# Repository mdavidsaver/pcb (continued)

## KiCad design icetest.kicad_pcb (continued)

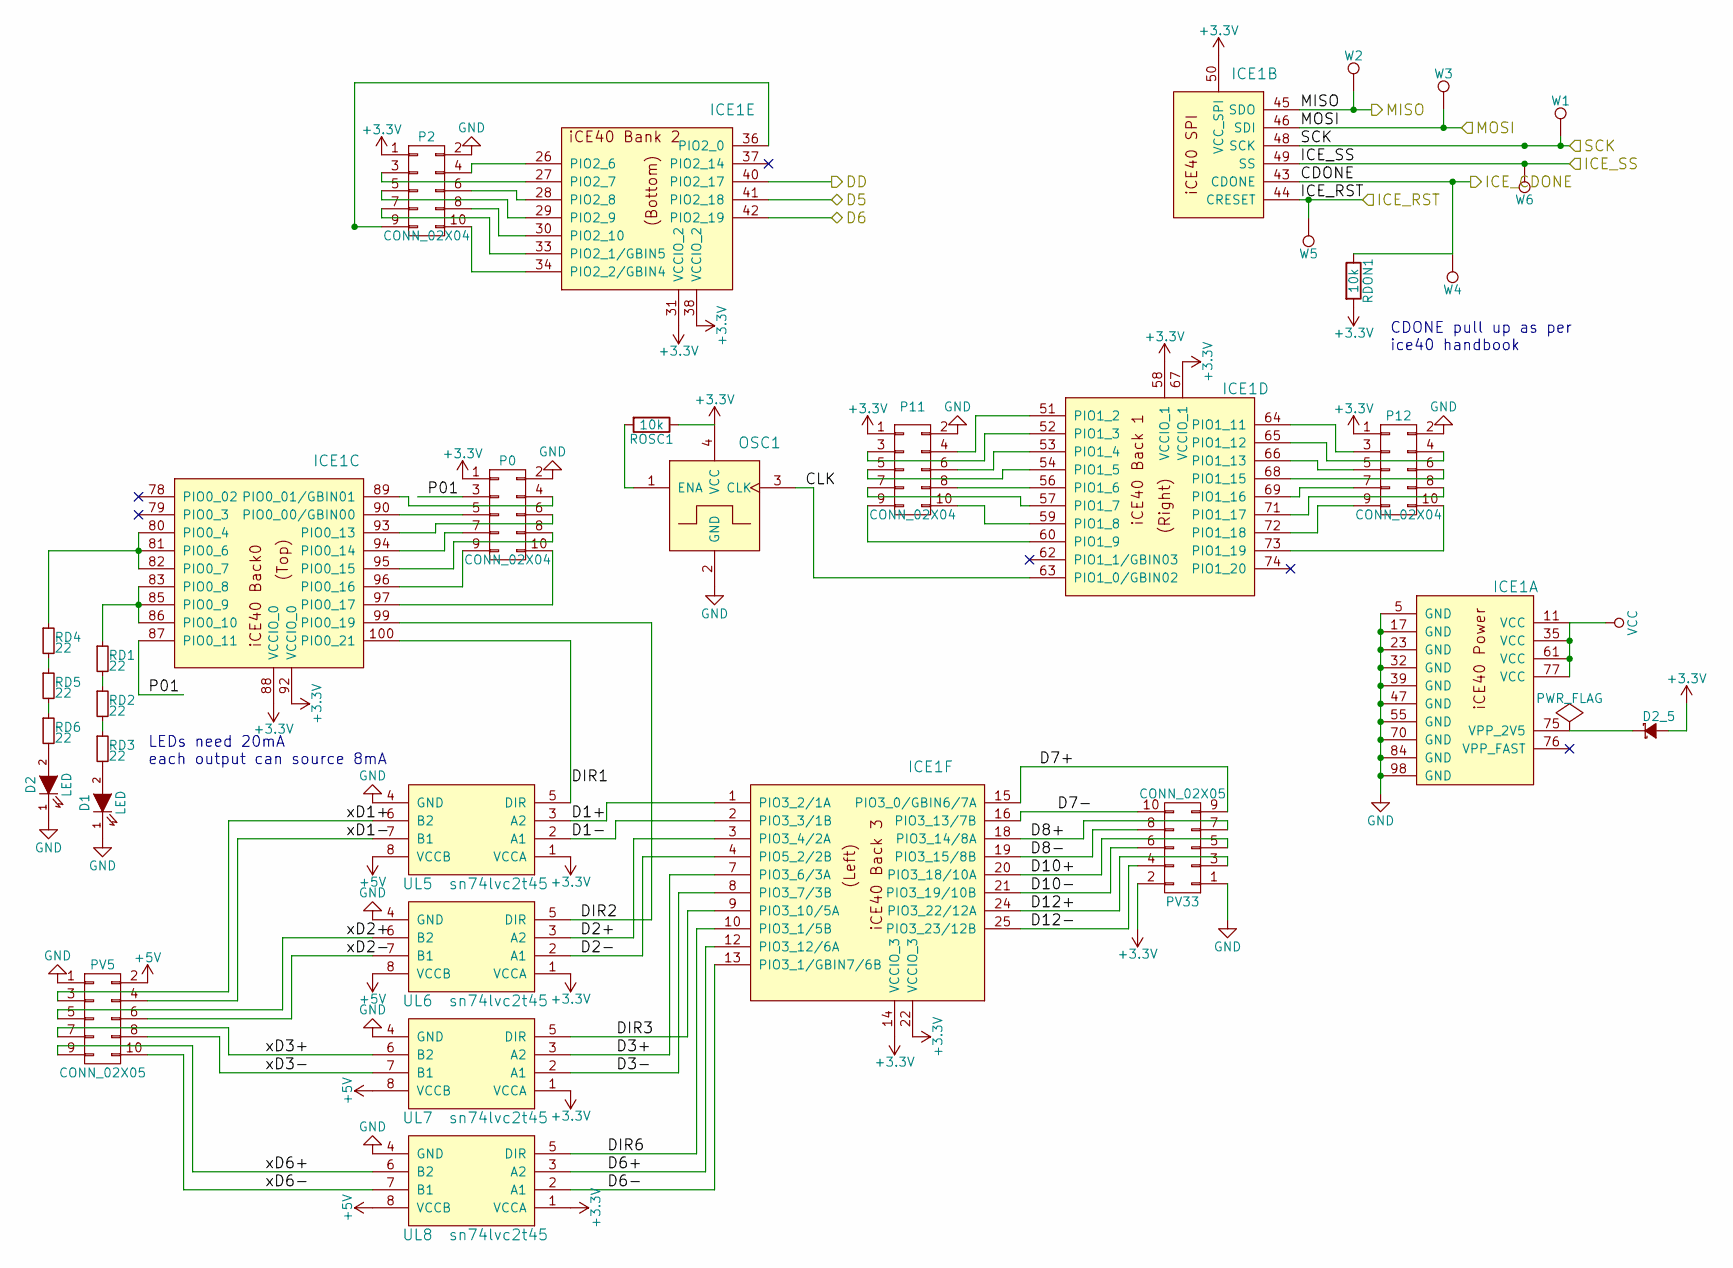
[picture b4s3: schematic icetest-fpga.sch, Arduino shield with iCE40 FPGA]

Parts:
D1, D2: LED; D_0603_HandSoldering
D2_5: D_Schottky_Small; D_0603_HandSoldering
ICE1: iCE40HX1K-VQ100; VQFP-100
OSC1: oscillator4; OSC_SMD_1
P0, P2, P11, P12: CONN_02X04; Pin_Header_Straight_2x05
PV5, PV33: CONN_02X05; Pin_Header_Straight_2x05
RD1, RD2, RD3, RD4, RD5, RD6: 22; R_0603_HandSoldering
RDON1: 10k; R_0603_HandSoldering
ROSC1: 10k; R_0603_HandSoldering
UL5, UL6, UL7, UL8: sn74lvc2t45; VSSOP-8
W1: SCLK; PINTST
W2: MISO; PINTST
W3: MOSI; PINTST
W4: CDONE; PINTST
W5: RST; PINTST
W6: SS; PINTST

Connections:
+3V3: D2_5.2 (A), ICE1.14 (VCCIO_3), ICE1.22 (VCCIO_3), ICE1.31 (VCCIO_2), ICE1.38 (VCCIO_2), ICE1.50 (VCC_SPI), ICE1.58 (VCCIO_1), ICE1.67 (VCCIO_1), ICE1.88 (VCCIO_0), ICE1.92 (VCCIO_0), OSC1.4 (VCC), P0.1, P2.1, P11.1, P12.1, PV33.2, RDON1.2, ROSC1.1, UL5.1 (VCCA), UL6.1 (VCCA), UL7.1 (VCCA), UL8.1 (VCCA); also elsewhere on the board
+5V: PV5.2, UL5.8 (VCCB), UL6.8 (VCCB), UL7.8 (VCCB), UL8.8 (VCCB); also elsewhere on the board
/Arduino Shield/D5: ICE1.41 (PIO2_18); also elsewhere on the board
/Arduino Shield/D6: ICE1.42 (PIO2_19); also elsewhere on the board
/Arduino Shield/DD: ICE1.40 (PIO2_17); also elsewhere on the board
/Arduino Shield/ICE_CDONE: ICE1.43 (CDONE), RDON1.1, W4.1; also elsewhere on the board
/Arduino Shield/ICE_RST: ICE1.44 (CRESET), W5.1; also elsewhere on the board
/Arduino Shield/ICE_SS: ICE1.49 (SS), W6.1; also elsewhere on the board
/Arduino Shield/MISO: ICE1.45 (SDO), W2.1; also elsewhere on the board
/Arduino Shield/MOSI: ICE1.46 (SDI), W3.1; also elsewhere on the board
/Arduino Shield/SCK: ICE1.48 (SCK), W1.1; also elsewhere on the board
/FPGA/CLK: ICE1.63 (PIO1_0/GBIN02), OSC1.3 (CLK); also elsewhere on the board
/FPGA/D1+: ICE1.1 (PIO3_2/1A), UL5.3 (A2)
/FPGA/D1-: ICE1.2 (PIO3_3/1B), UL5.2 (A1)
/FPGA/D2+: ICE1.3 (PIO3_4/2A), UL6.3 (A2)
/FPGA/D2-: ICE1.4 (PIO5_2/2B), UL6.2 (A1)
/FPGA/D3+: ICE1.7 (PIO3_6/3A), UL7.3 (A2)
/FPGA/D3-: ICE1.8 (PIO3_7/3B), UL7.2 (A1)
/FPGA/D6+: ICE1.12 (PIO3_12/6A), UL8.3 (A2)
/FPGA/D6-: ICE1.13 (PIO3_1/GBIN7/6B), UL8.2 (A1)
/FPGA/D7+: ICE1.15 (PIO3_0/GBIN6/7A), PV33.9
/FPGA/D7-: ICE1.16 (PIO3_13/7B), PV33.10
/FPGA/D8+: ICE1.18 (PIO3_14/8A), PV33.7
/FPGA/D8-: ICE1.19 (PIO3_15/8B), PV33.8
/FPGA/D10+: ICE1.20 (PIO3_18/10A), PV33.5
/FPGA/D10-: ICE1.21 (PIO3_19/10B), PV33.6
/FPGA/D12+: ICE1.24 (PIO3_22/12A), PV33.3
/FPGA/D12-: ICE1.25 (PIO3_23/12B), PV33.4
/FPGA/DIR1: ICE1.100 (PIO0_21), UL5.5 (DIR); also elsewhere on the board
/FPGA/DIR2: ICE1.99 (PIO0_19), UL6.5 (DIR); also elsewhere on the board
/FPGA/DIR3: ICE1.9 (PIO3_10/5A), UL7.5 (DIR); also elsewhere on the board
/FPGA/DIR6: ICE1.10 (PIO3_1/5B), UL8.5 (DIR); also elsewhere on the board
/FPGA/P01: ICE1.87 (PIO0_11), P0.3
/FPGA/xD1+: PV5.3, UL5.6 (B2)
/FPGA/xD1-: PV5.4, UL5.7 (B1)
/FPGA/xD2+: PV5.5, UL6.6 (B2)
/FPGA/xD2-: PV5.6, UL6.7 (B1)
/FPGA/xD3+: PV5.7, UL7.6 (B2)
/FPGA/xD3-: PV5.8, UL7.7 (B1)
/FPGA/xD6+: PV5.9, UL8.6 (B2)
/FPGA/xD6-: PV5.10, UL8.7 (B1)
GND: D1.1 (K), D2.1 (K), ICE1.5 (GND), ICE1.17 (GND), ICE1.23 (GND), ICE1.32 (GND), ICE1.39 (GND), ICE1.47 (GND), ICE1.55 (GND), ICE1.70 (GND), ICE1.84 (GND), ICE1.98 (GND), OSC1.2 (GND), P0.2, P2.2, P11.2, P12.2, PV5.1, PV33.1, UL5.4 (GND), UL6.4 (GND), UL7.4 (GND), UL8.4 (GND); also elsewhere on the board
unnamed: D1.2 (A), RD3.2
unnamed: D2.2 (A), RD6.2
unnamed: D2_5.1 (K), ICE1.75 (VPP_2V5)
unnamed: ICE1.26 (PIO2_6), P2.4
unnamed: ICE1.27 (PIO2_7), P2.3
unnamed: ICE1.28 (PIO2_8), P2.6
unnamed: ICE1.29 (PIO2_9), P2.5
unnamed: ICE1.30 (PIO2_10), P2.8
unnamed: ICE1.33 (PIO2_1/GBIN5), P2.7
unnamed: ICE1.34 (PIO2_2/GBIN4), P2.10
unnamed: ICE1.36 (PIO2_0), P2.9
unnamed: ICE1.51 (PIO1_2), P11.4
unnamed: ICE1.52 (PIO1_3), P11.3
unnamed: ICE1.53 (PIO1_4), P11.6
unnamed: ICE1.54 (PIO1_5), P11.5
unnamed: ICE1.56 (PIO1_6), P11.8
unnamed: ICE1.57 (PIO1_7), P11.7
unnamed: ICE1.59 (PIO1_8), P11.10
unnamed: ICE1.60 (PIO1_9), P11.9
unnamed: ICE1.64 (PIO1_11), P12.3
unnamed: ICE1.65 (PIO1_12), P12.4
unnamed: ICE1.66 (PIO1_13), P12.5
unnamed: ICE1.68 (PIO1_15), P12.6
unnamed: ICE1.69 (PIO1_16), P12.7
unnamed: ICE1.71 (PIO1_17), P12.8
unnamed: ICE1.72 (PIO1_18), P12.9
unnamed: ICE1.73 (PIO1_19), P12.10
unnamed: ICE1.80 (PIO0_4), ICE1.81 (PIO0_6), ICE1.82 (PIO0_7), RD4.1
unnamed: ICE1.83 (PIO0_8), ICE1.85 (PIO0_9), ICE1.86 (PIO0_10), RD1.1
unnamed: ICE1.89 (PIO0_01/GBIN01), P0.4
unnamed: ICE1.90 (PIO0_00/GBIN00), P0.5
unnamed: ICE1.93 (PIO0_13), P0.6
unnamed: ICE1.94 (PIO0_14), P0.7
unnamed: ICE1.95 (PIO0_15), P0.8
unnamed: ICE1.96 (PIO0_16), P0.9
unnamed: ICE1.97 (PIO0_17), P0.10
unnamed: OSC1.1 (ENA), ROSC1.2
unnamed: RD1.2, RD2.1
unnamed: RD2.2, RD3.1
unnamed: RD4.2, RD5.1
unnamed: RD5.2, RD6.1
VCC: ICE1.11 (VCC), ICE1.35 (VCC), ICE1.61 (VCC), ICE1.77 (VCC); also elsewhere on the board

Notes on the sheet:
LEDs need 20mA each output can source 8mA
CDONE pull up as per ice40 handbook

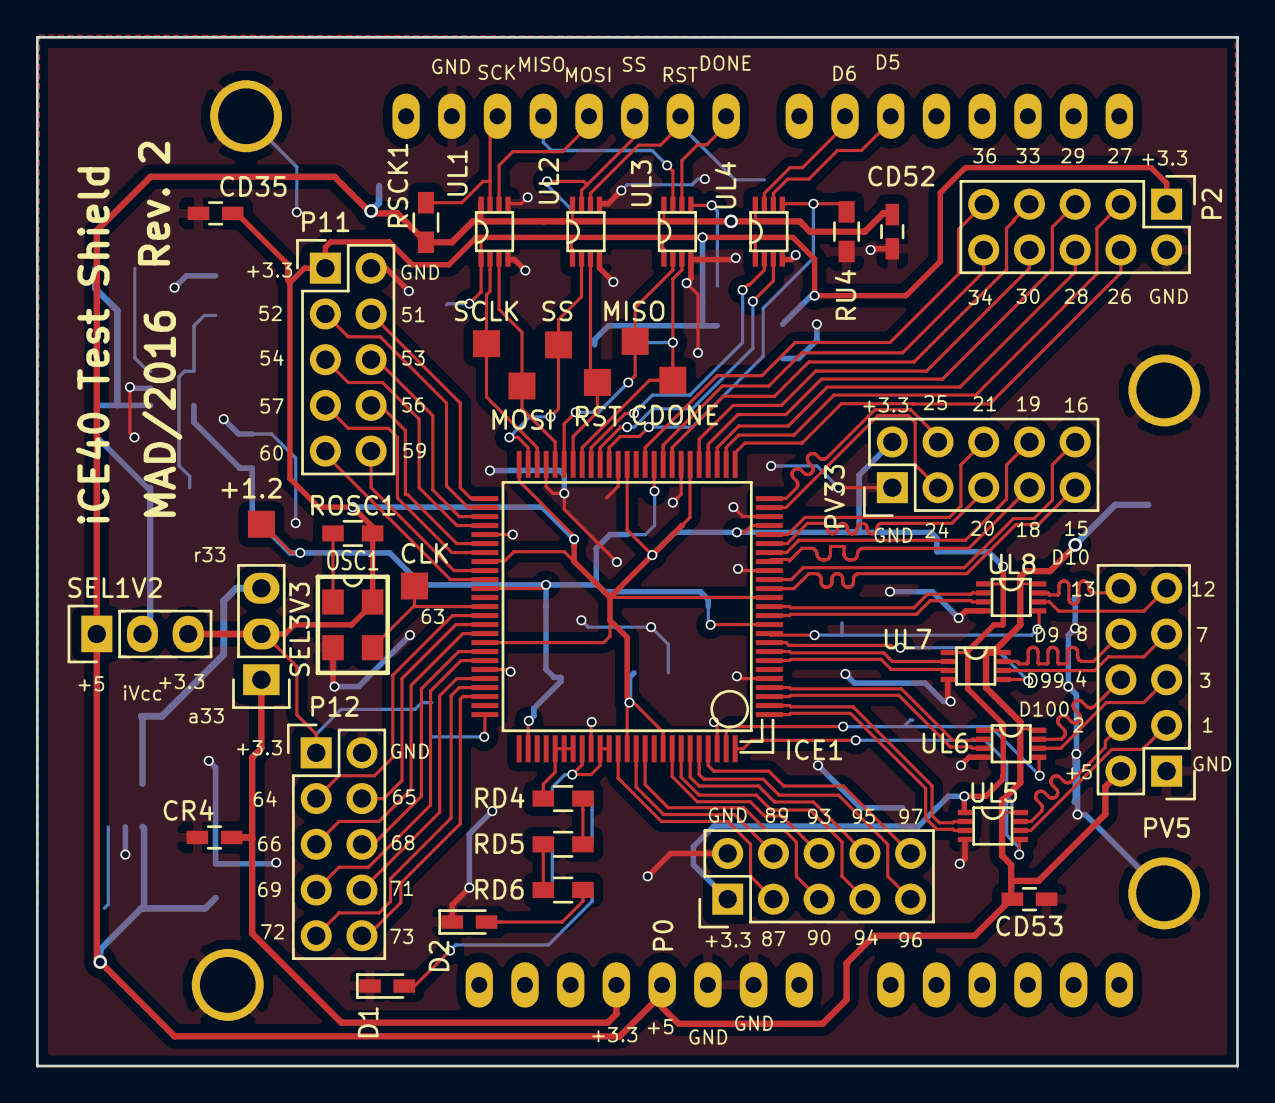
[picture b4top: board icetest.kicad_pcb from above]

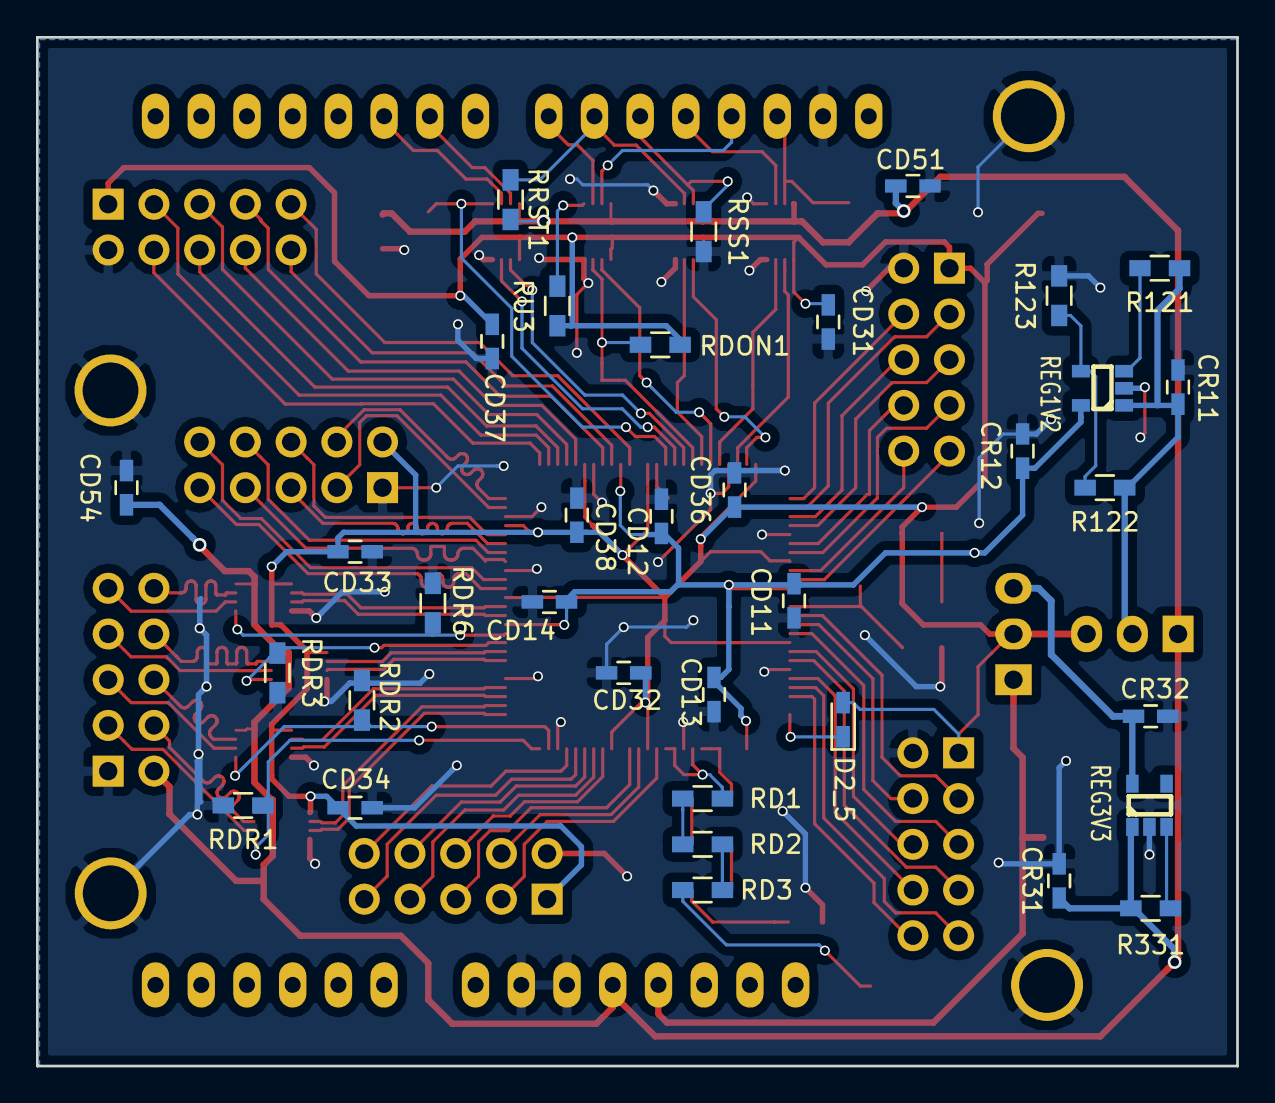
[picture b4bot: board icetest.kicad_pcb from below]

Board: 2 copper layers, 66.7 x 57.2 mm, 74 parts (35 on the bottom side), 99 nets.

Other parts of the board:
RDR1, RDR2, RDR3, RDR6: 10k; R_0603_HandSoldering
W7: CLK; Measurement_Point_Square-SMD-Pad_Small

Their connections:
/FPGA/CLK: W7.1; also elsewhere on the board
/FPGA/DIR1: RDR1.1; also elsewhere on the board
/FPGA/DIR2: RDR2.1; also elsewhere on the board
/FPGA/DIR3: RDR3.1; also elsewhere on the board
/FPGA/DIR6: RDR6.1; also elsewhere on the board
GND: RDR1.2, RDR2.2, RDR3.2, RDR6.2; also elsewhere on the board

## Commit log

2016-07-18 initial
2016-07-23 add SPI test points and verify footprints
2016-07-23 fix pad clearence
2016-07-23 route it
2016-08-02 fix ard symbol and route
2016-08-02 remove dup pins from symbols
2016-08-06 fix schematic bugs
    signal on N/C pin on ice40
    1.2V regulator R divider moved to input side
    Remove R divider for 3.3V (not needed for fixed V model)
2016-08-07 update layout
2016-08-07 add LED2 and update layout
2016-08-07 clean and oshpart rules
2016-08-07 scripts to generate and view gerbers
2016-08-07 fix solder mask gap and others
2016-08-07 more current for LEDs
2016-08-08 minor layout
2016-08-08 gerbshow in order
2016-08-08 add schematic notes
2016-10-08 add errata and notes
2016-10-09 switch level shifter
2016-10-10 redo layout
2016-10-10 more layout
2016-10-15 bom generation
2016-11-06 parts
2016-11-06 move to sub-dir
2016-12-05 start utherm
2016-12-05 icetest readme
2016-12-18 add opamp breakout
2016-12-25 start icedaq
2017-08-13 icedaq: update
2017-08-13 icedaq layout
2017-08-13 icedaq more
2017-08-14 minor
2017-08-20 icedaq: change input filter
2017-08-22 icedaq: layout take 2
2017-08-23 icedaq: relocate connectors
2017-08-23 icedaq rev 1
